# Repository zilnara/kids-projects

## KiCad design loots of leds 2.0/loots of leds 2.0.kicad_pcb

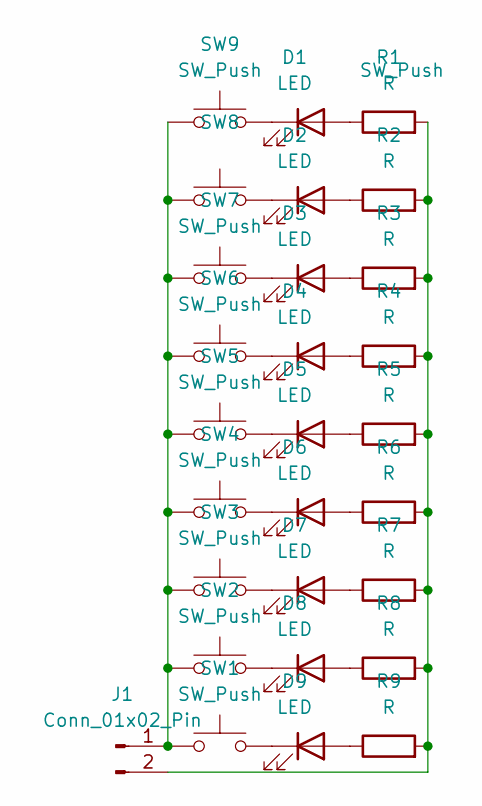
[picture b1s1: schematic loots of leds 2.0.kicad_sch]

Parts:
D1, D2, D3, D4, D5, D6, D7, D8, D9: LED; LED_D5.0mm_FlatTop
J1: Conn_01x02_Pin; PinHeader_2x01_P2.54mm_Vertical
R1, R2, R3, R4, R5, R6, R7, R8, R9: R; R_Axial_DIN0207_L6.3mm_D2.5mm_P10.16mm_Horizontal
SW1, SW2, SW3, SW4, SW5, SW6, SW7, SW8, SW9: SW_Push; SW_PUSH_6mm

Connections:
unnamed: D1.2 (A), R1.1
unnamed: D1.1 (K), SW9.2
unnamed: D2.2 (A), R2.1
unnamed: D2.1 (K), SW8.2
unnamed: D3.2 (A), R3.1
unnamed: D3.1 (K), SW7.2
unnamed: D4.2 (A), R4.1
unnamed: D4.1 (K), SW6.2
unnamed: D5.2 (A), R5.1
unnamed: D5.1 (K), SW5.2
unnamed: D6.2 (A), R6.1
unnamed: D6.1 (K), SW4.2
unnamed: D7.2 (A), R7.1
unnamed: D7.1 (K), SW3.2
unnamed: D8.2 (A), R8.1
unnamed: D8.1 (K), SW2.2
unnamed: D9.2 (A), R9.1
unnamed: D9.1 (K), SW1.2
unnamed: J1.1, SW1.1, SW2.1, SW3.1, SW4.1, SW5.1, SW6.1, SW7.1, SW8.1, SW9.1
unnamed: J1.2, R1.2, R2.2, R3.2, R4.2, R5.2, R6.2, R7.2, R8.2, R9.2

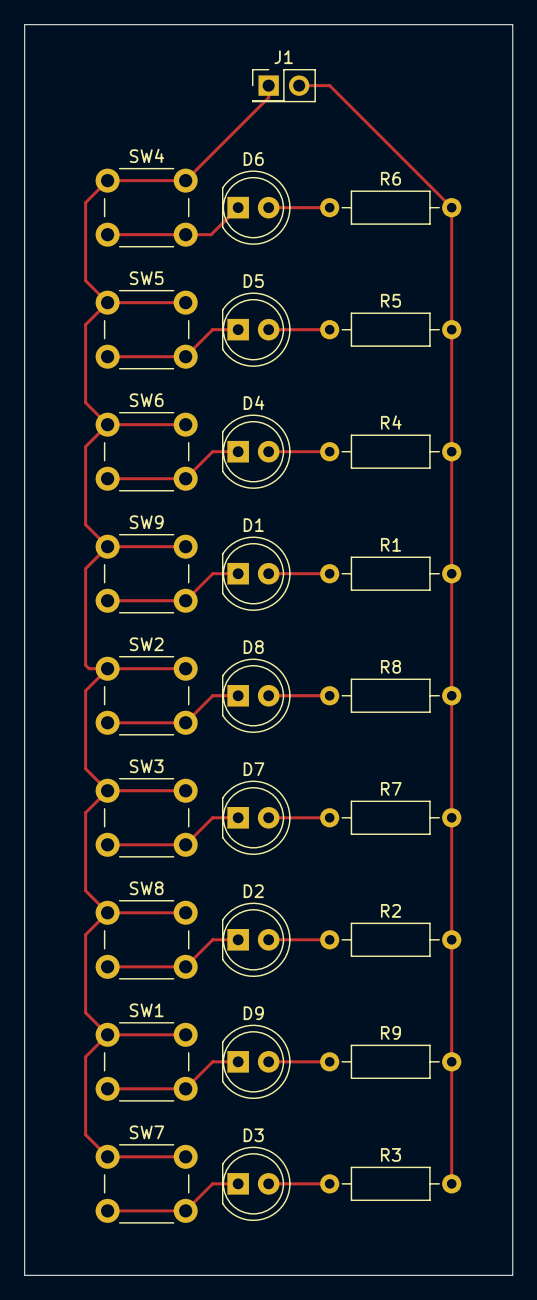
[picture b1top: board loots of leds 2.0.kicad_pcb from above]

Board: 2 copper layers, 40.6 x 104.1 mm, 28 parts (0 on the bottom side), 20 nets.

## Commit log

2023-05-27 Initial project setup
2023-05-27 Add power connections to LED sheet
2023-05-27 added a new key
2023-05-27 added extra switches
2023-05-28 more changes to keys
2023-05-29 a million more keys on row 2
2023-06-15 SHOULD BE DONE!!!!!!!
2023-06-20 moving PCB files into a more descriptive subdirectory
2023-06-20 add README
2023-06-23 i am really sure it is done now
2023-07-07 add a board with LEDs and buttons
